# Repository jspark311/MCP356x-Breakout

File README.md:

# MCP3564-Breakout

A breakout board for Microchip's 24-bit SPI ADC. The MCP3564 is a 24-bit sigma-delta ADC with support for up to eight single-ended, or four differential channels. It supports extensive oversampling depths, flexible MUX front-end, circuit burnout detection, adjustable gain, Vref from [0v - 3.6v], and optional internal oscillator.

#### [Hackaday.io Page](https://hackaday.io/project/168371-mcp3564-breakout)

#### [Order from Tindie](https://www.tindie.com/products/24263/)

------------------------

### What is in this repository:

**./doc**:  Location for documentation

**./KiCAD**:  Hardware design files

**./Arduino**:  Arduino driver

------------------------

Front (With OSC) | Back (With OSC)
:-------:|:------:
  | 
Front (No OSC) | Back (No OSC)
  |

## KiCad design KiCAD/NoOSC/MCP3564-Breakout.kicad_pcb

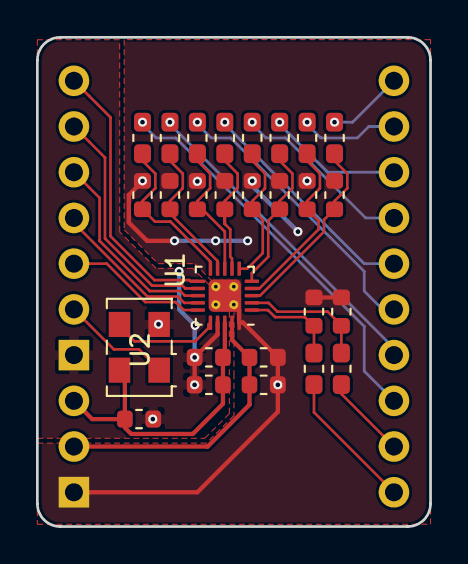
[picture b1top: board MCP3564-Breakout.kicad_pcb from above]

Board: 2 copper layers, 21.8 x 27.2 mm, 29 parts (0 on the bottom side), 31 nets.

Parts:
C0, C1, C2, C3, C4, C5, C6, C7, C11, C12: 0.1uF; C_0603_1608Metric
C8, C9, C10, C13, C14: 10uF; C_0603_1608Metric
J2, J3: Conn_01x08_Male; PinHeader_1x10_P2.54mm_Vertical
R0, R1, R2, R3, R4, R5, R6, R7, R8, R9: 100; R_0603_1608Metric_Pad1.05x0.95mm_HandSolder
U1: MCP3964; QFN-20-1EP_3x3mm_P0.45mm_EP1.6x1.6mm_ThermalVias
U2: 19.6608MHz OSC; Oscillator_SMD_EuroQuartz_XO53-4Pin_5.0x3.2mm

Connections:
/CH0: J3.1, R0.1
/CH1: J3.2, R1.1
/CH2: J3.3, R2.1
/CH3: J3.4, R3.1
/CH4: J3.5, R4.1
/CH5: J3.6, R5.1
/CH6: J3.7, R6.1
/CH7: J3.8, R7.1
/GNDA: C0.2, C1.2, C2.2, C3.2, C4.2, C5.2, C6.2, C7.2, C8.2, C11.1, C13.2, C14.1, J2.1, U1.20, U1.21
/GNDD: C9.2, C10.2, C12.1, J2.4, U1.17, U2.2
/MCLK: U1.16, U2.3
/OSC_EN: J2.5, U2.1
/REFIN+: C14.2, R8.2, U1.2
/REFIN-: C13.1, R9.2, U1.1
/SCK: J2.9, U1.12
/SDI: J2.8, U1.13
/SDO: J2.7, U1.14
/VddA: C8.1, C11.2, J2.2, U1.19
/VddD: C9.1, C10.1, C12.2, J2.3, U1.18, U2.4
/~CS: J2.10, U1.11
/~IRQ: J2.6, U1.15
unnamed: C0.1, R0.2, U1.3
unnamed: C1.1, R1.2, U1.4
unnamed: C2.1, R2.2, U1.5
unnamed: C3.1, R3.2, U1.6
unnamed: C4.1, R4.2, U1.7
unnamed: C5.1, R5.2, U1.8
unnamed: C6.1, R6.2, U1.9
unnamed: C7.1, R7.2, U1.10
unnamed: J3.9, R8.1
unnamed: J3.10, R9.1

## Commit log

2021-09-22 Finially collecting the mess for this repo. Initial commit.
2021-09-23 Fixing outdated example.
2021-09-23 Fixing versioning and deps.
2021-10-04 Updating entire project.
2021-10-04 README fix.
2021-10-04 Updating Arduino library to support the MCP3564R.
